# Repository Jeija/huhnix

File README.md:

# Huhnix
Huhnix is software for an automatic slider door, such as a door for a hen house (hence the name). The slider door opens automatically every morning at a set time and is operated with two buttons or via WiFi. Settings can be adjusted with WiFi device that can access the settings webpage. Huhnix uses two microprocessors that communicate over a UART interface.

## Pictures

## Documentation
### Main controller: AVR
The main processor receives inputs from two buttons that are used to make the doors slide up or down and keeps all the settings and keeps track of the time (so no need for a RTC).

### Secondary controller: ESP8266
The ESP8266 provides a configuration interface by acting as an access point that mobile devices can connect to in order to access a simple web interface. This web interface can be used to access system information such as the system clock and battery levels. The ESP8266 (e.g. within an ESP-01 module) is only active, when the main processor wakes it up. That is the case, when any of the slider control buttons have been pressed. This is crucial to save limited battery power. The battery can be charged using a solar panel. The ESP8266 software is based on the IoT SDK version 1.4 from Espressif.

### Controller communication protocol
#### Definitions
Due to restrictions of the ESP-01 module, the two processors have to communicate over the serial port. The protocol is as follows:
* Baudrate 9600 Baud, no parity, 8 bits, no stopbit, no flow control
* Each processor must always listen for commands and can always send commands. When a processor receives a command, it must answer immediately or perform the requested action and may not execute another command at the same time.
* If any unknown or unexpected string / command / ... is received by any processor, it has to be ignored. This is due to the fact that the ESP8266 SDK ROM outputs debug information, which cannot be disabled.
* Each command is terminated by "\r\n". The command itself may not contain any of these characters.

#### Commands
| ESP8266 command	| Description	|
|-----------------	|---------------------------------------------------------------------------------------------------------------------------------------------------------------------------------------------------------------------------------------------------------------------------------------------------------------------------------------------------------------------------------------------------------------------------------------------	|
| time	| For debugging only, outputs human-readable DCF77 time information	|
| dcf	| For debugging only, outputs debugging data on the DCF77 signal	|
| time_get	| To be used by the AVR controller. Outputs time data in a machine (and also human) readable form: Seconds, minutes, hours, date (of month), month, year (only last two digits) and day (of week) are transferred in this order as human-readable strings with a space in between each value. If no valid time value is available, the ESP8266 answers with the character x.	|

| AVR command	| Description	|
|---------------------	|----------------------------------------------------------------------------------------------------------------------------------------------------------------------------------------------------------------------------------------------------------------------------------------------------------------------------------------------	|
| slider_down	| Move the slider door down. Must be acknowledged by sending the string "sld_ok".	|
| slider_up	| Move the slider door up. Must be acknowledged by sending the string "slu_ok".	|
| systime_get	| Gets the current system time in the same format as time_get (for debugging and for Display on the web frontend).	|
| battery_get	| To be used by the ESP8266. Voltage and percent values are transferred as two human-readable numbers with a space in between them. The voltage value is transferred as an unsigned integer with the value being measured in 100mV (so a value of 123 indicates 12,3V). The percentage value is an estimated integer number between 0 and 100.	|
| opentime_get	| Get time at which to open the slider automatically (time of day). Hours and minutes are transferred as two human-readable integer numbers with a space in between them. An hour value of 25 indicates that the slider is not supposed to be opened at all.	|
| opentime_set <hours> <minutes>	| Tell AVR to open the slider at <hours>:<minutes> each day, where hours and minutes are integers seperate by a space. Must be acknowledged by sending the string "ots_ok"	|

### AVR hardware
The ATMega128A's fusebits are `E:FF, H:89, L:FF`, make sure to disable ATMega 103 compatibility mode! I use a cheap [chinese ATMega128A development board from LC Studio](http://www.lctech-inc.com/Hardware/Detail.aspx?id=68611f14-46cd-4676-95df-f1246689dbba) with the power LED desoldered in order to save power. A custom addon board (PCB design files in `hardware` directory, currently only tested with a prototype board) is stacked on top of the pin headers of the development board. This addon board has connectors for the DCF77 real time clock (I use the one from [conrad.de](http://www.conrad.de/ce/de/product/641138), for buttons, for 12V power sensing, the 5V power supply (provided by a step down converter from a lead-acid battery) and for a 2-channel relay board (HL-52 V 1.0).

## Attribution / License
The PCB design and schematic uses [Jerry Dunmire's ESP8266 KiCAD library](https://github.com/jdunmire/kicad-ESP8266) in the `hardware/libraries/ESP8266` directory, licensed under CC BY-SA 4.0. I license my hardware designs under the [CC BY-SA 4.0 license](https://creativecommons.org/licenses/by-sa/4.0/).

The ESP8266 software uses [Spritetm's libesphttpd with espfs](https://github.com/Spritetm/libesphttpd) in `esp8266/libesphttpd`. All my code is licensed under the [MIT license](http://opensource.org/licenses/MIT).

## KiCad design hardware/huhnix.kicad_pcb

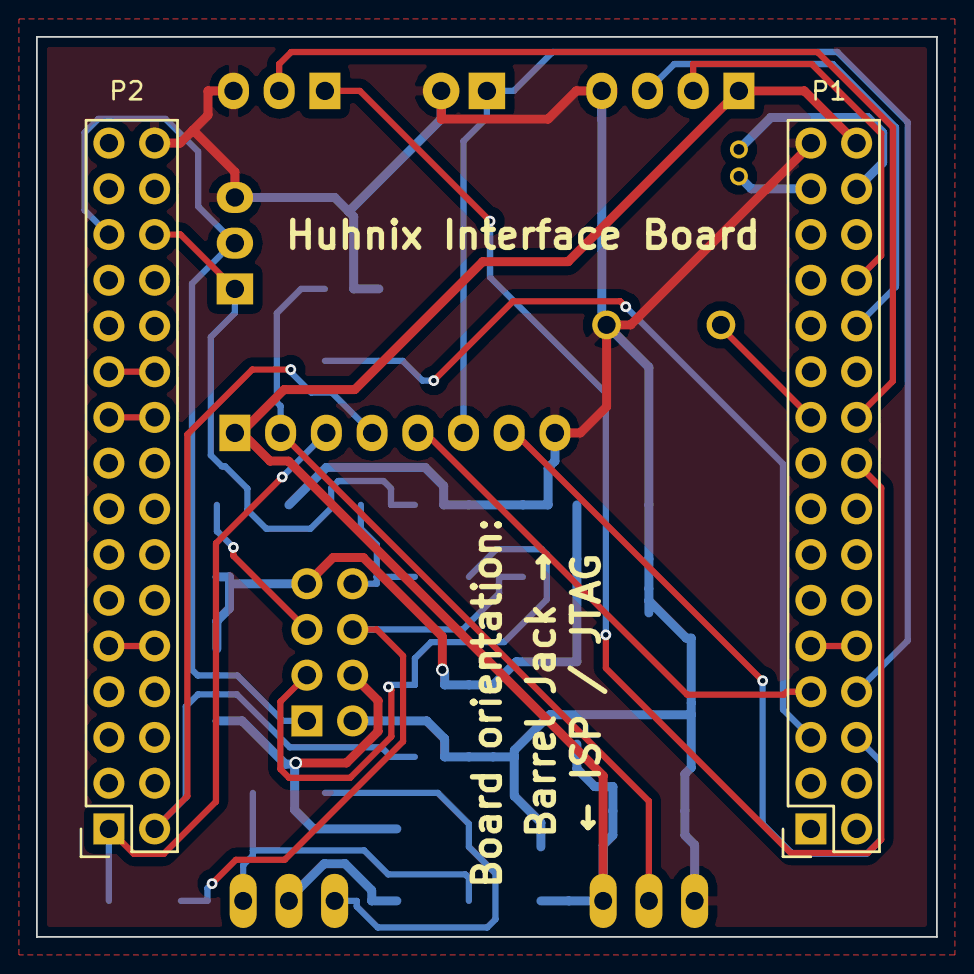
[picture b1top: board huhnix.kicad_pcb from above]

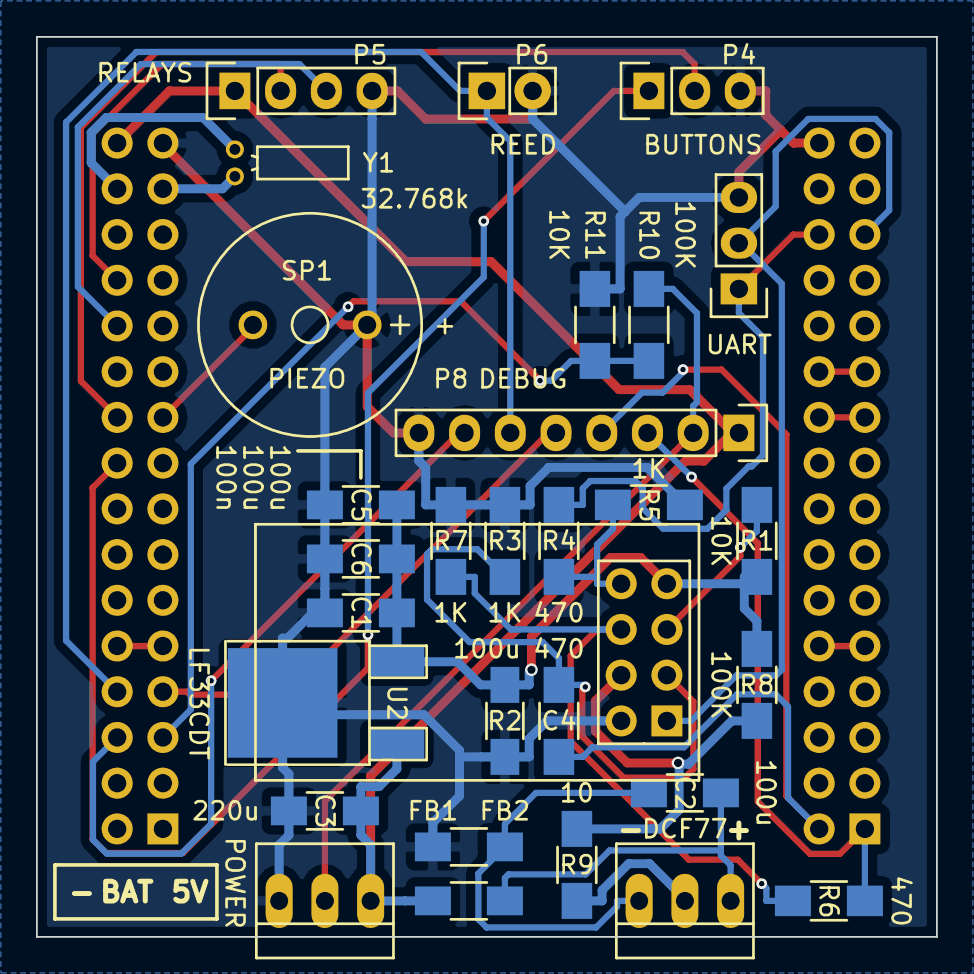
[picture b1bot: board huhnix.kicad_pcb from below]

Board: 2 copper layers, 50.0 x 50.0 mm, 32 parts (30 on the bottom side), 31 nets.

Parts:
C1: 100n; C_1206_HandSoldering
C2, C4, C5, C6: 100u; C_1206_HandSoldering
C3: 220u; C_1206_HandSoldering
FB1, FB2: FILTER; C_1206_HandSoldering
P1, P2: CONN_02X16; Socket_Strip_Straight_2x16
P3: DCF77; PINHEAD1-3
P4: BUTTONS; Pin_Header_Straight_1x03
P5: RELAYS; Pin_Header_Straight_1x04
P6: REED; Pin_Header_Straight_1x02
P7: POWER; PINHEAD1-3
P8: UART; Pin_Header_Straight_1x03
P9: DEBUG; Pin_Header_Straight_1x08
R1, R11: 10K; R_1206_HandSoldering
R2, R4, R6: 470; R_1206_HandSoldering
R3, R5, R7: 1K; R_1206_HandSoldering
R8, R10: 100K; R_1206_HandSoldering
R9: 10; R_1206_HandSoldering
SP1: PIEZO; MagneticBuzzer_ProSignal_ABT-410-RC
U1: ESP-01v090; ESP-01
U2: LF33CDT; TO-252-2Lead
Y1: 32.768k; Crystal_Round_Horizontal_2mm

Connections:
+3V3: C1.1, C4.1, C5.1, C6.1, R1.1, R8.1, U1.7, U2.3
+5V: C3.1, FB1.1, P1.32, P5.1, P7.1, P9.1, U2.1
+BATT: P7.2, P9.2, R10.1
/Aref: P1.9, P1.10
/PB2: P1.24, P5.3
/PB4: P1.26, P5.2
/PE4: P1.18, P4.1
/PE6: P1.20, P4.2
/PE7: P1.19, SP1.1
/PF0: P1.7, P9.5
/PF1: P1.8, P6.1, P9.6
/PF2: P1.5, R10.2, R11.1
/PF3: P1.6, P9.7
/PG0: P2.21, P2.22
/PG1: P2.19, P2.20
/PG2: P2.9, P2.10
/PG3: P1.30, Y1.1
/PG4: P1.29, Y1.2
DCF: P3.2, R9.2
ESP_EN: P2.2, P9.4, R2.1
ESP_PRGM: P2.1, P9.3, R6.1
GND: C1.2, C3.2, C4.2, C5.2, C6.2, FB2.1, P1.31, P2.32, P4.3, P5.4, P6.2, P7.3, P8.3, P9.8, R3.2, R5.2, R7.2, R11.2, SP1.2, U1.2, U2.2
unnamed: C2.1, FB1.2, P3.1
unnamed: C2.2, FB2.2, P3.3
unnamed: R1.2, U1.5
unnamed: R2.2, R3.1, U1.3
unnamed: R4.2, R5.1, U1.8
unnamed: R6.2, R7.1, U1.6
unnamed: R8.2, R9.1, U1.4
RXD: P2.27, P8.2, U1.1
TXD: P2.28, P8.1, R4.1

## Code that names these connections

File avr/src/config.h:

// UART1 configuration
#define BAUD 9600

// Buffer configurations, internals, ...
#define CMD_BUF_SIZE 40

// EEPROM layout
#define EEPROM_OFFSET 0x00

/*** Hardware connections ***/
// Buttons
#define BUTTON_PORT PORTE
#define BUTTON_DDR DDRE
#define BUTTON_PIN PINE
#define BUTTON1_BIT PE4
#define BUTTON2_BIT PE6
#define BUTTON_EICR EICRB
#define BUTTON1_ISC 0x00
#define BUTTON2_ISC 0x00
#define BUTTON1_INT (1<<INT4)
#define BUTTON2_INT (1<<INT6)
#define BUTTON1_vect INT4_vect
#define BUTTON2_vect INT6_vect

// Slider reed contact
#define REED_PORT PORTF
#define REED_DDR DDRF
#define REED_PIN PINF
#define REED_BIT PF1

// Slider motors (to relays)
#define RELAY_PORT PORTB
#define RELAY_DDR DDRB
#define RELAY1_BIT PB2
#define RELAY2_BIT PB4

// Piezo loudspeaker
#define PIEZO_PORT PORTE
#define PIEZO_DDR DDRE
#define PIEZO_BIT PE7

// Battery, factor depends on voltage devider specifics
#define BATT_ADC 2
#define BATT_MIN 115
#define BATT_MAX 130
#define BATT_ADC_FACTOR 116

// ESP8266
#define ESP_PORT PORTA
#define ESP_DDR DDRA
#define ESP_ENABLE PA0
#define ESP_PROGRAM PA1

// Input value counts
#define INPUT_VALID_COUNT 1000
#define SLIDER_UP_EMERGENCY_STOP_COUNT 1200000

// Timing
#define SLIDER_DOWN_TIME 6
#define SLIDER_UP_TIME_MAX 25
#define TIME_UPDATE_INTERVAL 10
#define TIME_UPDATE_MAXAGE 20
#define TIME_UPDATE_WARN_AGE ((uint64_t)3600 * 24 * 7)
#define MAX_WAKE_TIME (60 * 6)

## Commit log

2015-08-22 Initial upload
2015-08-24 Fix integer length of TIME_UPDATE_WARN_AGE from 16-bit to 64-bit
    The 16-bit integer caused time-not-synchronized warnings at startup even
    though the AVR had perfectly good, recent time information.
    Some minor cleanups.
2015-10-18 Update to ESP IoT SDK V1.4, update libesphttpd, allow setting time over WiFi (client's system time)
